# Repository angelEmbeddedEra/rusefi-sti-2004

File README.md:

# FAQ

Q: How do I build the board package?

A: ``hellen-create-board`` in this folder (EmbeddedEra/KiCad scripting/hellen; docker, KiCad 10). Output lands in ``boards/<board>-<rev>/``. There is no GitHub workflow.

Q: How do I get latest hellen-one?

A: ``git submodule update --remote hellen-one kicad6-libraries``, then rebuild and commit.

Q: I get error 'Cannot stat xx-yy__zz.kicad_pcb: No such file' but files are right there?

A: please do not use dashes and underscore symbols in file names.

Q: Automation says that aux_axis_origin is missing?

A: aux_axis_origin is required, please place it in the appropriate corner.

Q: I get "Cannot parse position" with negative value?

A: Please move origin point into left-bottom corner of the board since we cannot parse negative coordinates at the moment. See https://github.com/andreika-git/hellen-one/issues/349

Q: I am placing an order with JLCPCB and component orientation all looks wrong?!

A: See https://github.com/rusefi/uaefi/?tab=readme-ov-file#q-ive-place-an-order-with-jlcpcb-and-i-see-scary-looking-wrong-orientation

Q: What about firmware?

A: See https://github.com/rusefi/fw-custom-hellen144-f4 and https://github.com/rusefi/rusefi/wiki/Custom-Firmware

Q: Automation seems to work but files are not updated?

A: automation requires that you use default branch 'main'

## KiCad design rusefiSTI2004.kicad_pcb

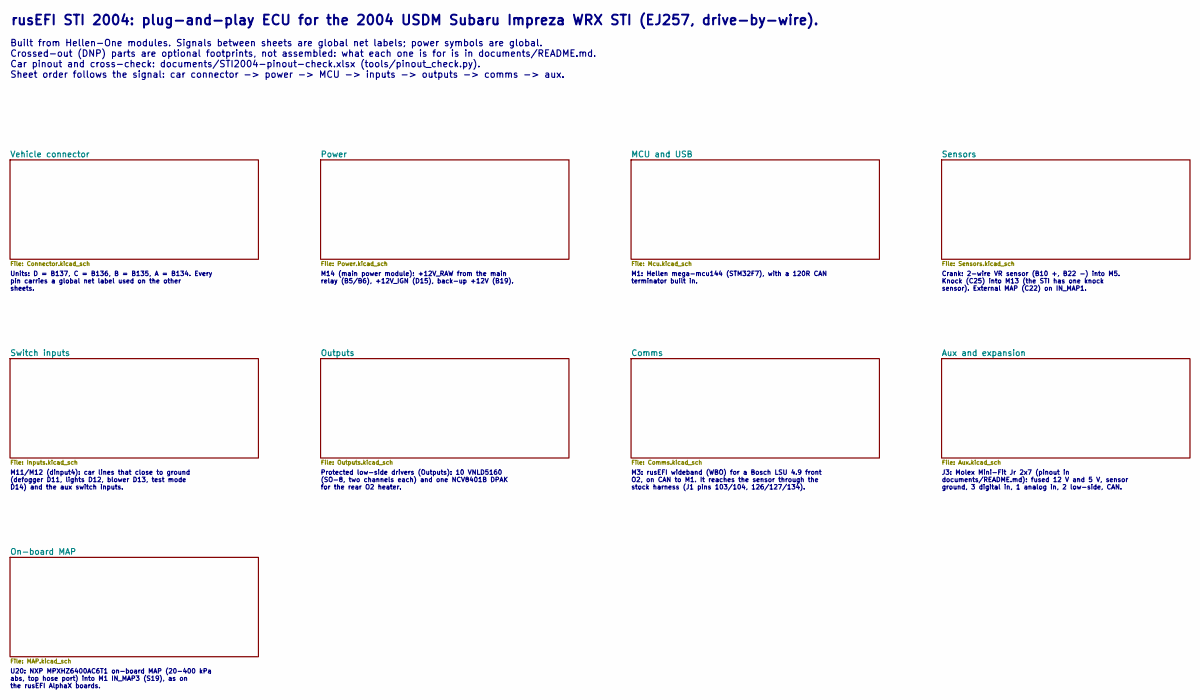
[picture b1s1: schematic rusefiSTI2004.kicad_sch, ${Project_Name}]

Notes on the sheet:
Units: D = B137, C = B136, B = B135, A = B134. Every pin carries a global net label used on the other sheets.
Built from Hellen-One modules. Signals between sheets are global net labels; power symbols are global. Crossed-out (DNP) parts are optional footprints, not assembled: what each one is for is in documents/README.md. Car pinout and cross-check: documents/STI2004-pinout-check.xlsx (tools/pinout_check.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
M14 (main power module): +12V_RAW from the main relay (B5/B6), +12V_IGN (D15), back-up +12V (B19).
J3: Molex Mini-Fit Jr 2x7 (pinout in documents/README.md): fused 12 V and 5 V, sensor ground, 3 digital in, 1 analog in, 2 low-side, CAN.
M11/M12 (dinput4): car lines that close to ground (defogger D11, lights D12, blower D13, test mode D14) and the aux switch inputs.
M3: rusEFI wideband (WBO) for a Bosch LSU 4.9 front O2, on CAN to M1. It reaches the sensor through the stock harness (J1 pins 103/104, 126/127/134).
Crank: 2-wire VR sensor (B10 +, B22 -) into M5. Knock (C25) into M13 (the STI has one knock sensor). External MAP (C22) on IN_MAP1.
M1: Hellen mega-mcu144 (STM32F7), with a 120R CAN terminator built in.
rusEFI STI 2004: plug-and-play ECU for the 2004 USDM Subaru Impreza WRX STI (EJ257, drive-by-wire).
Protected low-side drivers (Outputs): 10 VNLD5160 (SO-8, two channels each) and one NCV8401B DPAK for the rear O2 heater.
U20: NXP MPXHZ6400AC6T1 on-board MAP (20-400 kPa abs, top hose port) into M1 IN_MAP3 (S19), as on the rusEFI AlphaX boards.

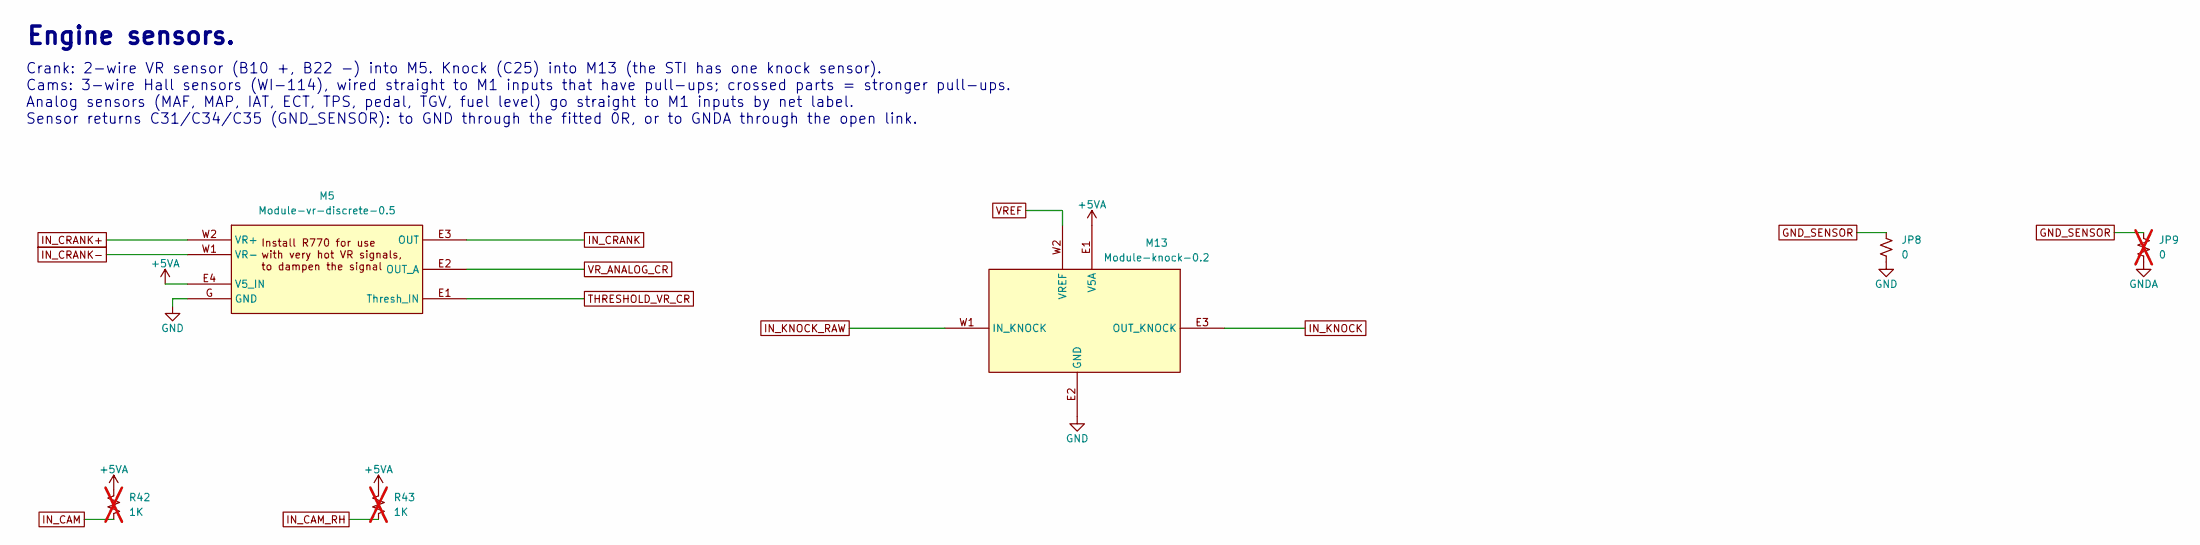
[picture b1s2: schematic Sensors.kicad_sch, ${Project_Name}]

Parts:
JP8: 0; R_0805_2012Metric; Manufacturer Part Number RC0805JR-070RL; LCSC C17477
JP9: 0; R_0805_2012Metric; Manufacturer Part Number RC0805JR-070RL; LCSC C17477; not fitted
M5: Module-vr-discrete-0.5; vr-discrete
M13: Module-knock-0.2; knock
R42, R43: 1K; R_0603_1608Metric; Manufacturer Part Number RC0603FR-071KL; LCSC C22548; not fitted

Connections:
+5VA: M5.E4 (V5_IN), M13.E1 (V5A), R42.2, R43.2; also elsewhere on the board
GNDA: JP9.2; also elsewhere on the board
GND_SENSOR: JP8.1, JP9.1; also elsewhere on the board
IN_CAM: R42.1; also elsewhere on the board
IN_CAM_RH: R43.1; also elsewhere on the board
IN_CRANK: M5.E3 (OUT); also elsewhere on the board
IN_CRANK+: M5.W2 (VR+); also elsewhere on the board
IN_CRANK-: M5.W1 (VR-); also elsewhere on the board
IN_KNOCK: M13.E3 (OUT_KNOCK); also elsewhere on the board
IN_KNOCK_RAW: M13.W1 (IN_KNOCK); also elsewhere on the board
THRESHOLD_VR_CR: M5.E1 (Thresh_IN); also elsewhere on the board
VREF: M13.W2 (VREF); also elsewhere on the board
VR_ANALOG_CR: M5.E2 (OUT_A); also elsewhere on the board

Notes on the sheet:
Engine sensors.
Crank: 2-wire VR sensor (B10 +, B22 -) into M5. Knock (C25) into M13 (the STI has one knock sensor). Cams: 3-wire Hall sensors (WI-114), wired straight to M1 inputs that have pull-ups; crossed parts = stronger pull-ups. Analog sensors (MAF, MAP, IAT, ECT, TPS, pedal, TGV, fuel level) go straight to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

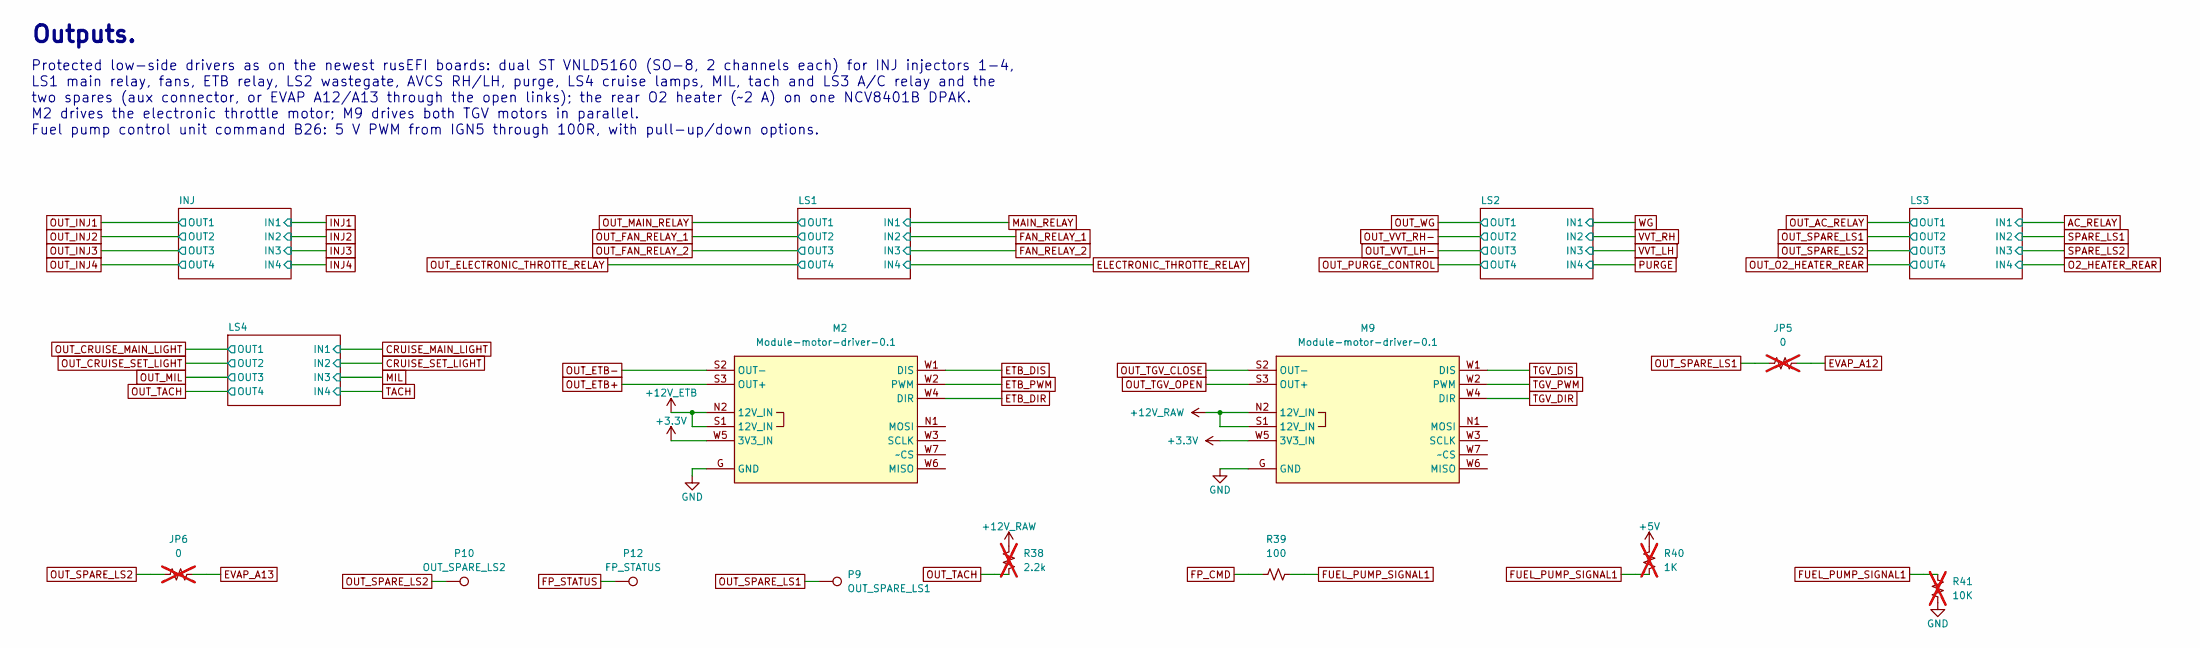
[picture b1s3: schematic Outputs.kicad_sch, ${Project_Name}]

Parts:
JP5, JP6: 0; R_0805_2012Metric; Manufacturer Part Number RC0805JR-070RL; LCSC C17477; not fitted
M2, M9: Module-motor-driver-0.1; motor-driver
P9: OUT_SPARE_LS1; TestPoint_THTPad_D2.0mm_Drill1.0mm
P10: OUT_SPARE_LS2; TestPoint_THTPad_D2.0mm_Drill1.0mm
P12: FP_STATUS; TestPoint_THTPad_D2.0mm_Drill1.0mm
R38: 2.2k; R_0805_2012Metric; Manufacturer Part Number RC0805JR-072K2L; LCSC C17520; not fitted
R39: 100; R_0603_1608Metric; Manufacturer Part Number RC0603FR-07100RL; LCSC C105588
R40: 1K; R_0603_1608Metric; Manufacturer Part Number RC0603FR-071KL; LCSC C22548; not fitted
R41: 10K; R_0603_1608Metric; Manufacturer Part Number RC0603FR-0710KL; LCSC C98220; not fitted

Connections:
+3.3V: M2.W5 (3V3_IN), M9.W5 (3V3_IN); also elsewhere on the board
+5V: R40.2; also elsewhere on the board
+12V_ETB: M2.N2 (12V_IN), M2.S1 (12V_IN); also elsewhere on the board
+12V_RAW: M9.N2 (12V_IN), M9.S1 (12V_IN), R38.2; also elsewhere on the board
ETB_DIR: M2.W4 (DIR); also elsewhere on the board
ETB_DIS: M2.W1 (DIS); also elsewhere on the board
ETB_PWM: M2.W2 (PWM); also elsewhere on the board
EVAP_A12: JP5.2; also elsewhere on the board
EVAP_A13: JP6.2; also elsewhere on the board
FP_CMD: R39.1; also elsewhere on the board
FP_STATUS: P12.1; also elsewhere on the board
FUEL_PUMP_SIGNAL1: R39.2, R40.1, R41.1; also elsewhere on the board
OUT_ETB+: M2.S3 (OUT+); also elsewhere on the board
OUT_ETB-: M2.S2 (OUT-); also elsewhere on the board
OUT_SPARE_LS1: JP5.1, P9.1; also elsewhere on the board
OUT_SPARE_LS2: JP6.1, P10.1; also elsewhere on the board
OUT_TACH: R38.1; also elsewhere on the board
OUT_TGV_CLOSE: M9.S2 (OUT-); also elsewhere on the board
OUT_TGV_OPEN: M9.S3 (OUT+); also elsewhere on the board
TGV_DIR: M9.W4 (DIR); also elsewhere on the board
TGV_DIS: M9.W1 (DIS); also elsewhere on the board
TGV_PWM: M9.W2 (PWM); also elsewhere on the board

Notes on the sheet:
Outputs.
Protected low-side drivers as on the newest rusEFI boards: dual ST VNLD5160 (SO-8, 2 channels each) for INJ injectors 1-4, LS1 main relay, fans, ETB relay, LS2 wastegate, AVCS RH/LH, purge, LS4 cruise lamps, MIL, tach and LS3 A/C relay and the two spares (aux connector, or EVAP A12/A13 through the 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

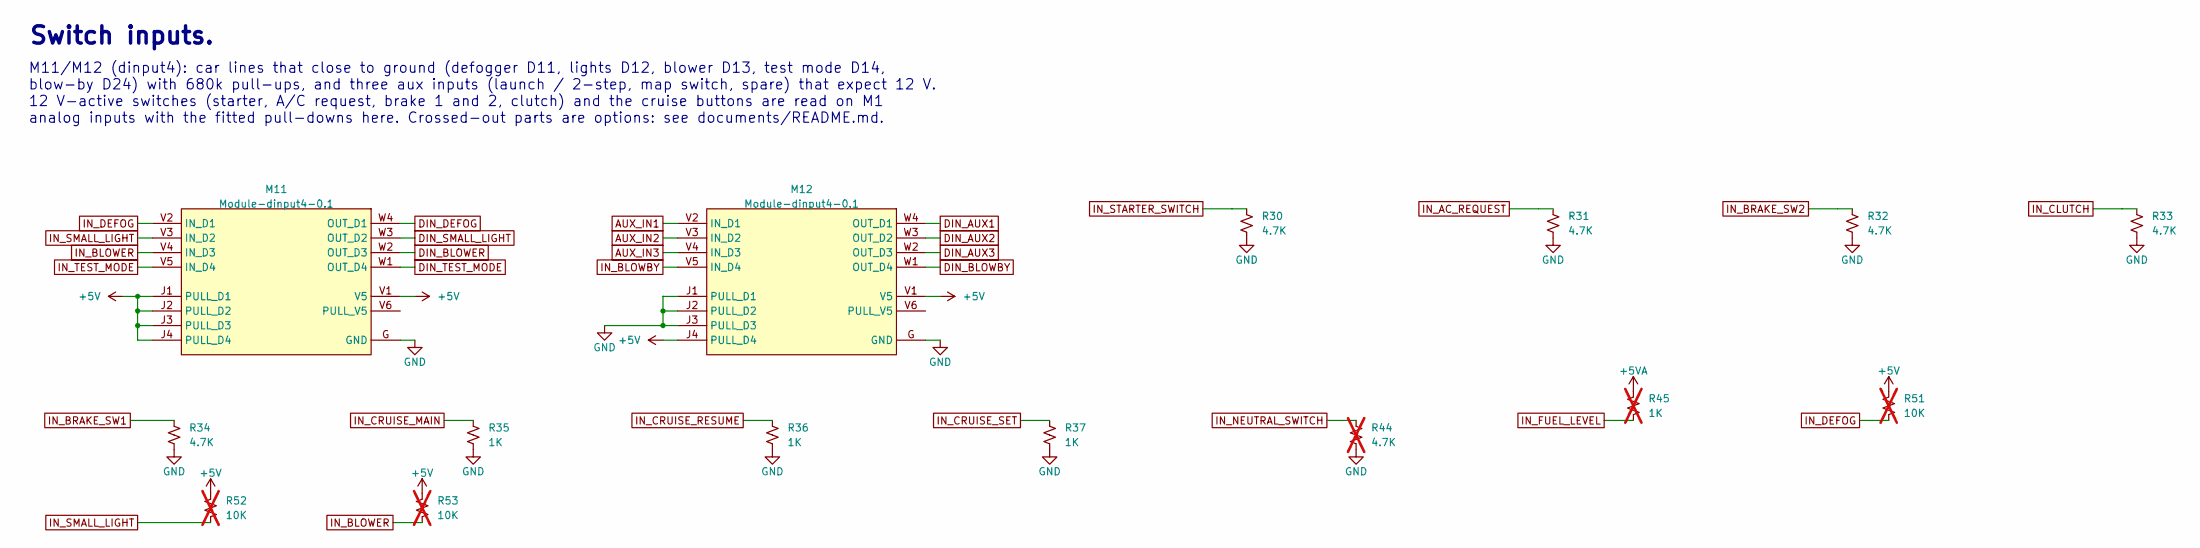
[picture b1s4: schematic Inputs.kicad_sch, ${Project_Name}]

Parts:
M11, M12: Module-dinput4-0.1; dinput4
R30, R31, R32, R33, R34: 4.7K; R_0603_1608Metric; Manufacturer Part Number RC0603FR-074K7L; LCSC C99782
R35, R36, R37: 1K; R_1206_3216Metric; Manufacturer Part Number ERJ-U08F1001V
R44: 4.7K; R_0603_1608Metric; Manufacturer Part Number RC0603FR-074K7L; LCSC C99782; not fitted
R45: 1K; R_0603_1608Metric; Manufacturer Part Number RC0603FR-071KL; LCSC C22548; not fitted
R51, R52, R53: 10K; R_0603_1608Metric; Manufacturer Part Number RC0603FR-0710KL; LCSC C98220; not fitted

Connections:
+5V: M11.J1 (PULL_D1), M11.J2 (PULL_D2), M11.J3 (PULL_D3), M11.J4 (PULL_D4), M11.V1 (V5), M12.J4 (PULL_D4), M12.V1 (V5), R51.2, R52.2, R53.2; also elsewhere on the board
+5VA: R45.2; also elsewhere on the board
AUX_IN1: M12.V2 (IN_D1); also elsewhere on the board
AUX_IN2: M12.V3 (IN_D2); also elsewhere on the board
AUX_IN3: M12.V4 (IN_D3); also elsewhere on the board
DIN_AUX1: M12.W4 (OUT_D1); also elsewhere on the board
DIN_AUX2: M12.W3 (OUT_D2); also elsewhere on the board
DIN_AUX3: M12.W2 (OUT_D3); also elsewhere on the board
DIN_BLOWBY: M12.W1 (OUT_D4); also elsewhere on the board
DIN_BLOWER: M11.W2 (OUT_D3); also elsewhere on the board
DIN_DEFOG: M11.W4 (OUT_D1); also elsewhere on the board
DIN_SMALL_LIGHT: M11.W3 (OUT_D2); also elsewhere on the board
DIN_TEST_MODE: M11.W1 (OUT_D4); also elsewhere on the board
IN_AC_REQUEST: R31.1; also elsewhere on the board
IN_BLOWBY: M12.V5 (IN_D4); also elsewhere on the board
IN_BLOWER: M11.V4 (IN_D3), R53.1; also elsewhere on the board
IN_BRAKE_SW1: R34.1; also elsewhere on the board
IN_BRAKE_SW2: R32.1; also elsewhere on the board
IN_CLUTCH: R33.1; also elsewhere on the board
IN_CRUISE_MAIN: R35.1; also elsewhere on the board
IN_CRUISE_RESUME: R36.1; also elsewhere on the board
IN_CRUISE_SET: R37.1; also elsewhere on the board
IN_DEFOG: M11.V2 (IN_D1), R51.1; also elsewhere on the board
IN_FUEL_LEVEL: R45.1; also elsewhere on the board
IN_NEUTRAL_SWITCH: R44.1; also elsewhere on the board
IN_SMALL_LIGHT: M11.V3 (IN_D2), R52.1; also elsewhere on the board
IN_STARTER_SWITCH: R30.1; also elsewhere on the board
IN_TEST_MODE: M11.V5 (IN_D4); also elsewhere on the board

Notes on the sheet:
Switch inputs.
M11/M12 (dinput4): car lines that close to ground (defogger D11, lights D12, blower D13, test mode D14, blow-by D24) with 680k pull-ups, and three aux inputs (launch / 2-step, map switch, spare) that expect 12 V. 12 V-active switches (starter, A/C request, brake 1 and 2, clutch) and the cruise butt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

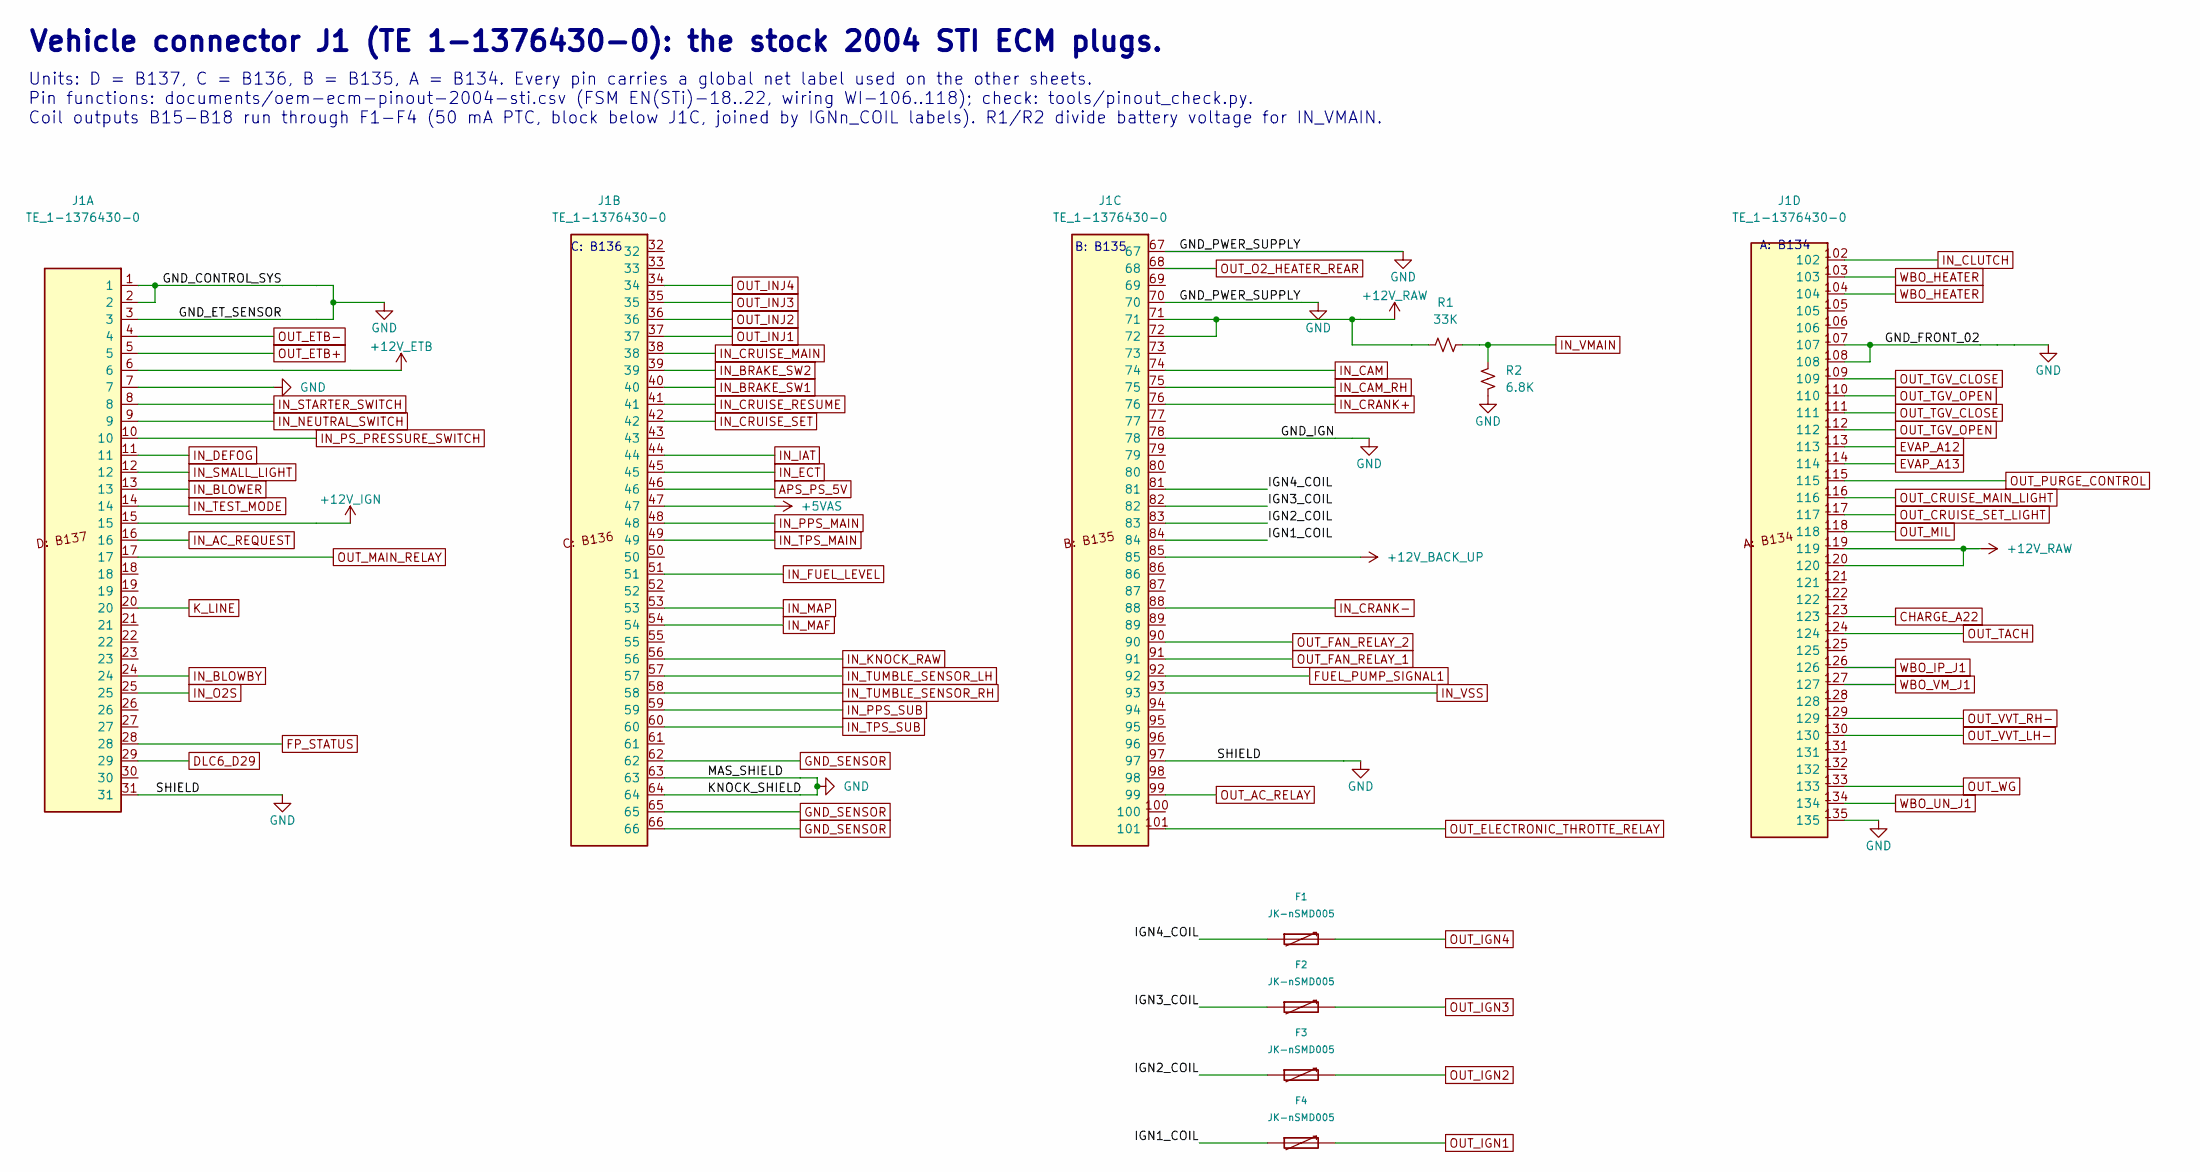
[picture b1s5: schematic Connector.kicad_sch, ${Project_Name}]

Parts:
F1, F2, F3, F4: JK-nSMD005; Fuse_1206_3216Metric; Manufacturer Part Number JK-nSMD005; LCSC C369153
J1: TE_1-1376430-0; Manufacturer Part Number 1-1376430-0
R1: 33K; R_0603_1608Metric; Manufacturer Part Number RC0603FR-0733KL; LCSC C126359
R2: 6.8K; R_0603_1608Metric; Manufacturer Part Number RC0603FR-076K8L; LCSC C114632

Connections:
+5VAS: J1.47; also elsewhere on the board
+12V_BACK_UP: J1.85; also elsewhere on the board
+12V_ETB: J1.6; also elsewhere on the board
+12V_IGN: J1.15; also elsewhere on the board
+12V_RAW: J1.71, J1.72, J1.119, J1.120, R1.1; also elsewhere on the board
/Vehicle connector/IGN1_COIL: F4.1, J1.84
/Vehicle connector/IGN2_COIL: F3.1, J1.83
/Vehicle connector/IGN3_COIL: F2.1, J1.82
/Vehicle connector/IGN4_COIL: F1.1, J1.81
APS_PS_5V: J1.46; also elsewhere on the board
CHARGE_A22: J1.123; also elsewhere on the board
DLC6_D29: J1.29; also elsewhere on the board
EVAP_A12: J1.113; also elsewhere on the board
EVAP_A13: J1.114; also elsewhere on the board
FP_STATUS: J1.28; also elsewhere on the board
FUEL_PUMP_SIGNAL1: J1.92; also elsewhere on the board
GND_SENSOR: J1.62, J1.65, J1.66; also elsewhere on the board
IN_AC_REQUEST: J1.16; also elsewhere on the board
IN_BLOWBY: J1.24; also elsewhere on the board
IN_BLOWER: J1.13; also elsewhere on the board
IN_BRAKE_SW1: J1.40; also elsewhere on the board
IN_BRAKE_SW2: J1.39; also elsewhere on the board
IN_CAM: J1.74; also elsewhere on the board
IN_CAM_RH: J1.75; also elsewhere on the board
IN_CLUTCH: J1.102; also elsewhere on the board
IN_CRANK+: J1.76; also elsewhere on the board
IN_CRANK-: J1.88; also elsewhere on the board
IN_CRUISE_MAIN: J1.38; also elsewhere on the board
IN_CRUISE_RESUME: J1.41; also elsewhere on the board
IN_CRUISE_SET: J1.42; also elsewhere on the board
IN_DEFOG: J1.11; also elsewhere on the board
IN_ECT: J1.45; also elsewhere on the board
IN_FUEL_LEVEL: J1.51; also elsewhere on the board
IN_IAT: J1.44; also elsewhere on the board
IN_KNOCK_RAW: J1.56; also elsewhere on the board
IN_MAF: J1.54; also elsewhere on the board
IN_MAP: J1.53; also elsewhere on the board
IN_NEUTRAL_SWITCH: J1.9; also elsewhere on the board
IN_O2S: J1.25; also elsewhere on the board
IN_PPS_MAIN: J1.48; also elsewhere on the board
IN_PPS_SUB: J1.59; also elsewhere on the board
IN_PS_PRESSURE_SWITCH: J1.10; also elsewhere on the board
IN_SMALL_LIGHT: J1.12; also elsewhere on the board
IN_STARTER_SWITCH: J1.8; also elsewhere on the board
IN_TEST_MODE: J1.14; also elsewhere on the board
IN_TPS_MAIN: J1.49; also elsewhere on the board
IN_TPS_SUB: J1.60; also elsewhere on the board
IN_TUMBLE_SENSOR_LH: J1.57; also elsewhere on the board
IN_TUMBLE_SENSOR_RH: J1.58; also elsewhere on the board
IN_VMAIN: R1.2, R2.2; also elsewhere on the board
IN_VSS: J1.93; also elsewhere on the board
K_LINE: J1.20; also elsewhere on the board
OUT_AC_RELAY: J1.99; also elsewhere on the board
OUT_CRUISE_MAIN_LIGHT: J1.116; also elsewhere on the board
OUT_CRUISE_SET_LIGHT: J1.117; also elsewhere on the board
OUT_ELECTRONIC_THROTTE_RELAY: J1.101; also elsewhere on the board
OUT_ETB+: J1.5; also elsewhere on the board
OUT_ETB-: J1.4; also elsewhere on the board
OUT_FAN_RELAY_1: J1.91; also elsewhere on the board
OUT_FAN_RELAY_2: J1.90; also elsewhere on the board
OUT_IGN1: F4.2; also elsewhere on the board
OUT_IGN2: F3.2; also elsewhere on the board
OUT_IGN3: F2.2; also elsewhere on the board
OUT_IGN4: F1.2; also elsewhere on the board
OUT_INJ1: J1.37; also elsewhere on the board
OUT_INJ2: J1.36; also elsewhere on the board
OUT_INJ3: J1.35; also elsewhere on the board
OUT_INJ4: J1.34; also elsewhere on the board
OUT_MAIN_RELAY: J1.17; also elsewhere on the board
OUT_MIL: J1.118; also elsewhere on the board
OUT_O2_HEATER_REAR: J1.68; also elsewhere on the board
OUT_PURGE_CONTROL: J1.115; also elsewhere on the board
OUT_TACH: J1.124; also elsewhere on the board
OUT_TGV_CLOSE: J1.109, J1.111; also elsewhere on the board
OUT_TGV_OPEN: J1.110, J1.112; also elsewhere on the board
OUT_VVT_LH-: J1.130; also elsewhere on the board
OUT_VVT_RH-: J1.129; also elsewhere on the board
OUT_WG: J1.133; also elsewhere on the board
WBO_HEATER: J1.103, J1.104; also elsewhere on the board
WBO_IP_J1: J1.126; also elsewhere on the board
WBO_UN_J1: J1.134; also elsewhere on the board
WBO_VM_J1: J1.127; also elsewhere on the board

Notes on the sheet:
Units: D = B137, C = B136, B = B135, A = B134. Every pin carries a global net label used on the other sheets. Pin functions: documents/oem-ecm-pinout-2004-sti.csv (FSM EN(STi)-18..22, wiring WI-106..118); check: tools/pinout_check.py. Coil outputs B15-B18 run through F1-F4 (50 mA PTC, block below J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
Vehicle connector J1 (TE 1-1376430-0): the stock 2004 STI ECM plugs.
B: B135
A: B134
C: B136

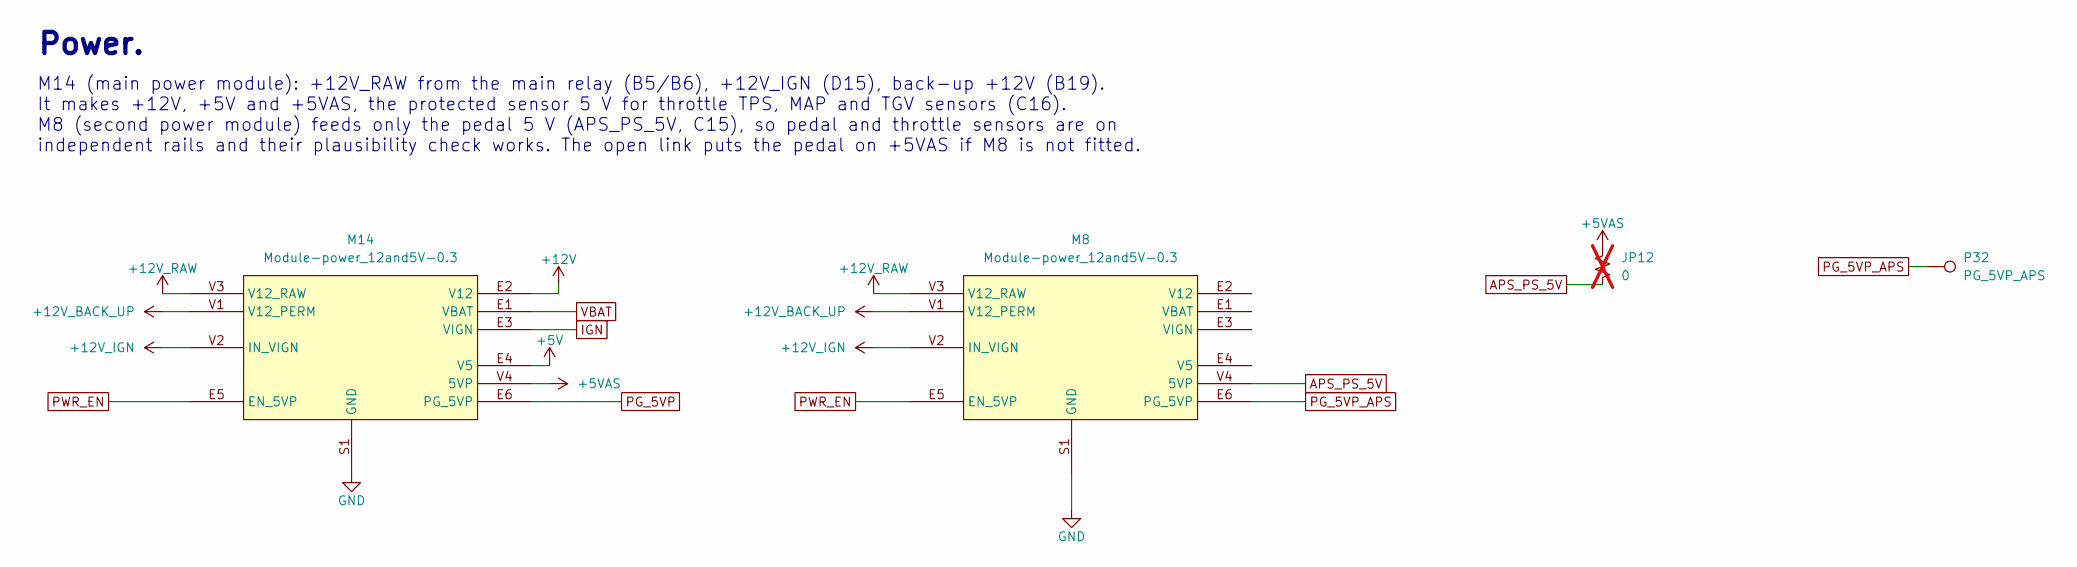
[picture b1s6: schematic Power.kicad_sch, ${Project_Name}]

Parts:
JP12: 0; R_0805_2012Metric; Manufacturer Part Number RC0805JR-070RL; LCSC C17477; not fitted
M8, M14: Module-power_12and5V-0.3; power_12and5V
P32: PG_5VP_APS; TestPoint_THTPad_D2.0mm_Drill1.0mm

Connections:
+5V: M14.E4 (V5); also elsewhere on the board
+5VAS: JP12.2, M14.V4 (5VP); also elsewhere on the board
+12V: M14.E2 (V12); also elsewhere on the board
+12V_BACK_UP: M8.V1 (V12_PERM), M14.V1 (V12_PERM); also elsewhere on the board
+12V_IGN: M8.V2 (IN_VIGN), M14.V2 (IN_VIGN); also elsewhere on the board
+12V_RAW: M8.V3 (V12_RAW), M14.V3 (V12_RAW); also elsewhere on the board
APS_PS_5V: JP12.1, M8.V4 (5VP); also elsewhere on the board
IGN: M14.E3 (VIGN); also elsewhere on the board
PG_5VP: M14.E6 (PG_5VP); also elsewhere on the board
PG_5VP_APS: M8.E6 (PG_5VP), P32.1
PWR_EN: M8.E5 (EN_5VP), M14.E5 (EN_5VP); also elsewhere on the board
VBAT: M14.E1 (VBAT); also elsewhere on the board

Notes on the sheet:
Power.
M14 (main power module): +12V_RAW from the main relay (B5/B6), +12V_IGN (D15), back-up +12V (B19). It makes +12V, +5V and +5VAS, the protected sensor 5 V for throttle TPS, MAP and TGV sensors (C16). M8 (second power module) feeds only the pedal 5 V (APS_PS_5V, C15), so pedal and throttle sensors ar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

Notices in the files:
parts and their libraries:
Power symbol creates a global label with name \"+12V\". Copied from KiCad library power:+12V (KiCad 10.0), CC-BY-SA 4.0 with the KiCad library exception.
